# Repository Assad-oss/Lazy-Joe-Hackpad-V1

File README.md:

Essentially the project started as me wanting to find out more about firmware and how it can be integrated with MCUs. 
Since I had no (real) need for any macro actions, I just decided to keep my design clean & simple, creating nifty volume up-down and brightness up-down buttons. Also created a rotary encoder to act as the tab button when rotated.

Features:
  4 buttons that turn volume up, volume down, brightness up, brightness down respectively (from 1-4)
  .0.91 inch OLED, SSD1306. Programmed with circuit python to display the switch number when a button is pressed.
  EC11 rotary encoder that corresponds to the tab key.

    My finished schematic, next time I make a similiar design I plan to just use labels to connect components and their legs to a GPIO pin. basically what was done with the OLED but also applied to switches (and other arbitrary/miscallaneous components used).

The PCB design I found fairly simplistic, since KiCad is already able to put components on a pcb format once you have assigned it a footprint in the schematic.
After that, routing and rearrangement of components fortunately went smoothly. In hindsight, I probably should have made it slightly larger with a more unique layout (can be remedied if I ever try the keyboard tutorial).

The CAD model - certainly the hardest part of my design. I have never used 3d software (atleast not to this extent) before, so it was a very steep learning curve. But eventually through looking at tutorials (and ample help from the hackboard tutorial) - I was able to gain some digital literacy and learn enough features to make the case. I also used a 3d model of the pcb to use in the assembled step file.

The 3D viewer tool in KiCad enables to see my PCB in a stimulated, 3D format. I saved this as a step file and imported it into the assembled hackpad.

Finally, the BOM list. ALl of the components I will be using are going to be included in the free kit provided - so there is no extra cost or grant I require.However, I have still made a list for clarity.

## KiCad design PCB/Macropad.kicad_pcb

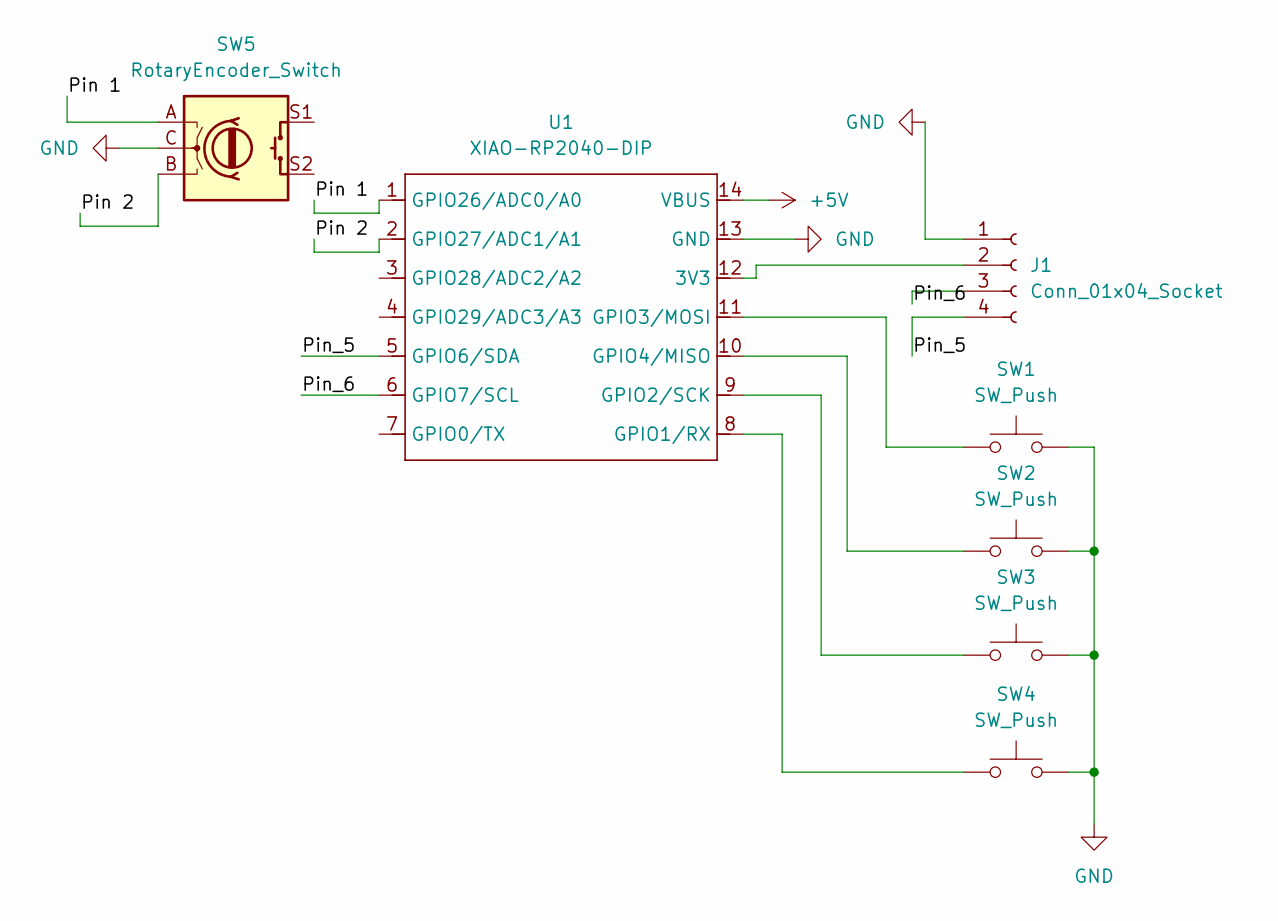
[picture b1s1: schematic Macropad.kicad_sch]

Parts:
J1: Conn_01x04_Socket; OLED_0.91_128x32
SW1, SW2, SW3, SW4: SW_Push; SW_Cherry_MX_1.00u_PCB
SW5: RotaryEncoder_Switch; RotaryEncoder_Alps_EC11E-Switch_Vertical_H20mm_CircularMoun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
U1: XIAO-RP2040-DIP

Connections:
+5V: U1.14 (VBUS)
/Pin 1: SW5.A, U1.1 (GPIO26/ADC0/A0)
/Pin 2: SW5.B, U1.2 (GPIO27/ADC1/A1)
/Pin_5: J1.4, U1.5 (GPIO6/SDA)
/Pin_6: J1.3, U1.6 (GPIO7/SCL)
GND: J1.1, SW1.2, SW2.2, SW3.2, SW4.2, SW5.C, U1.13 (GND)
unnamed: J1.2, U1.12 (3V3)
unnamed: SW4.1, U1.8 (GPIO1/RX)
unnamed: SW3.1, U1.9 (GPIO2/SCK)
unnamed: SW1.1, U1.11 (GPIO3/MOSI)
unnamed: SW2.1, U1.10 (GPIO4/MISO)

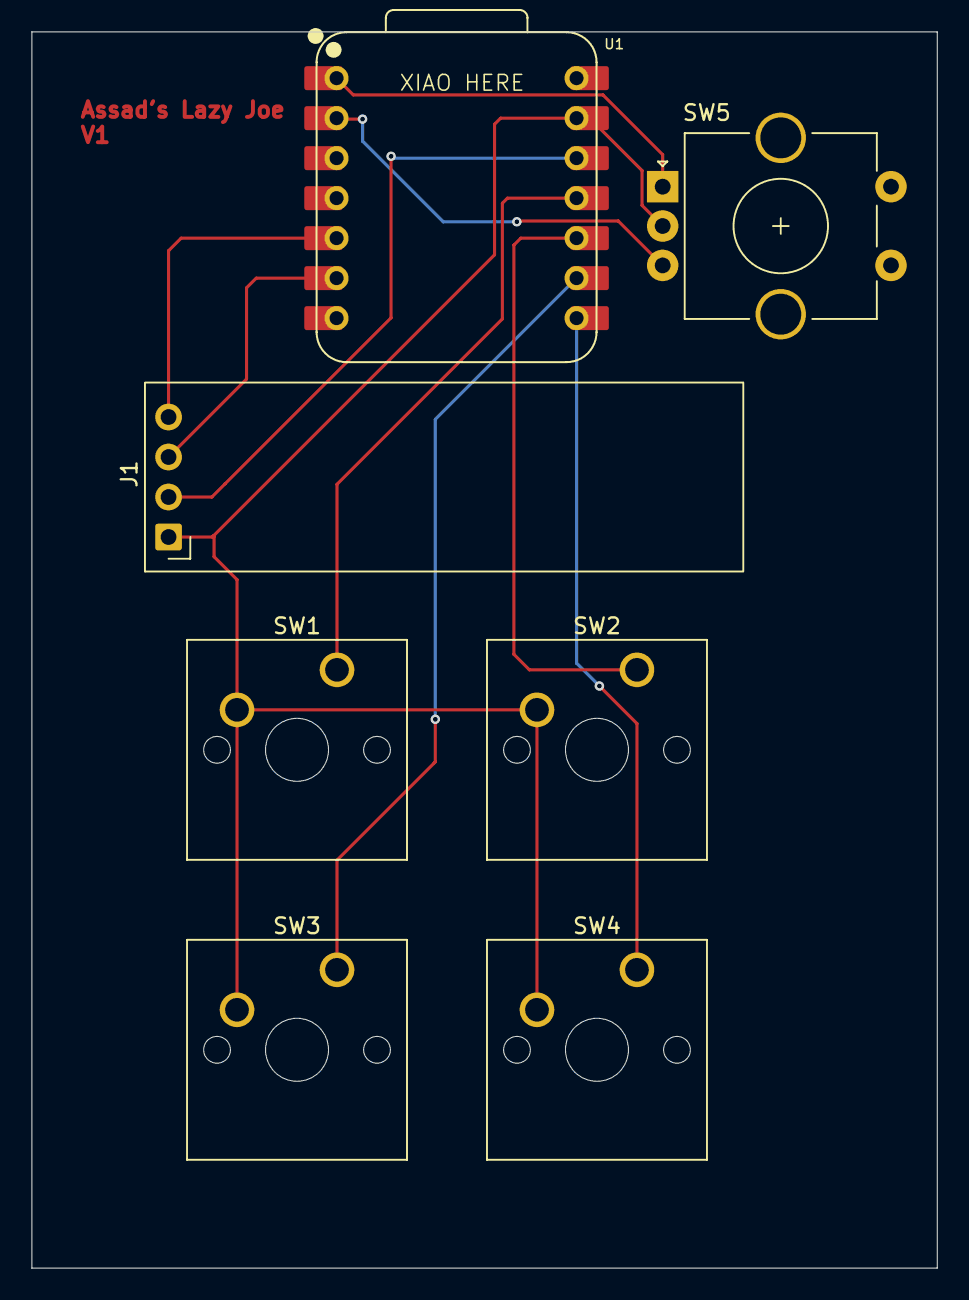
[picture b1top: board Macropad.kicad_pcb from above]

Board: 2 copper layers, 57.5 x 78.5 mm, 7 parts (0 on the bottom side), 10 nets.

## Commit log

2026-01-13 Create cad
2026-01-13 Create placeholder
